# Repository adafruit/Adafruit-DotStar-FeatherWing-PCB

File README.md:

## Adafruit DotStar FeatherWing PCB

<a href="http://www.adafruit.com/products/3449"><br/>
Click here to purchase one from the Adafruit shop</a>

PCB files for the Adafruit DotStar FeatherWing. Format is EagleCAD schematic and board layout

For more details, check out the product page at
* http://www.adafruit.com/products/3449

### Description

A Feather board without ambition is a Feather board without FeatherWings! This is the DotStar FeatherWing, a 6x12 RGB LED Add-on For All Feather Boards! Using our Feather Stacking Headers or Feather Female Headers you can connect a FeatherWing on top or bottom of your Feather board and make your Feather board strut like a peacock at a rave.

Put on your sunglasses before staring into these 72 configurable RGB LEDs, they are super bright! Arranged in a 6x12 matrix, each 2mm by 2mm sized RGB pixel is individually addressable. Only two pins are required to control all the LEDs. On the bottom we have jumpers for the Data and Clock lines so you can change them from the defaults. Works with any/all of our Feathers! You can cut the default jumper traces and use any pins you like

To make it easy to start, the LEDs are by default powered from either the USB power line or Battery power line, whichever is higher. Two Schottky diodes are used to switch between the two. This power arrangement is able to handle 1 Amp of constant current draw and maybe 2A peak, so not a good way to make a flashlight. It's better for colorful effects. A power MOSFET is set up and connected to the ENABLE pin on the Feather so that when the Feather is disabled, the wing will also cut power.

### License

Adafruit invests time and resources providing this open source design, please support Adafruit and open-source hardware by purchasing products from [Adafruit](https://www.adafruit.com)!

Designed by Limor Fried/Ladyada for Adafruit Industries.

Creative Commons Attribution/Share-Alike, all text above must be included in any redistribution. See license.txt for additional details.

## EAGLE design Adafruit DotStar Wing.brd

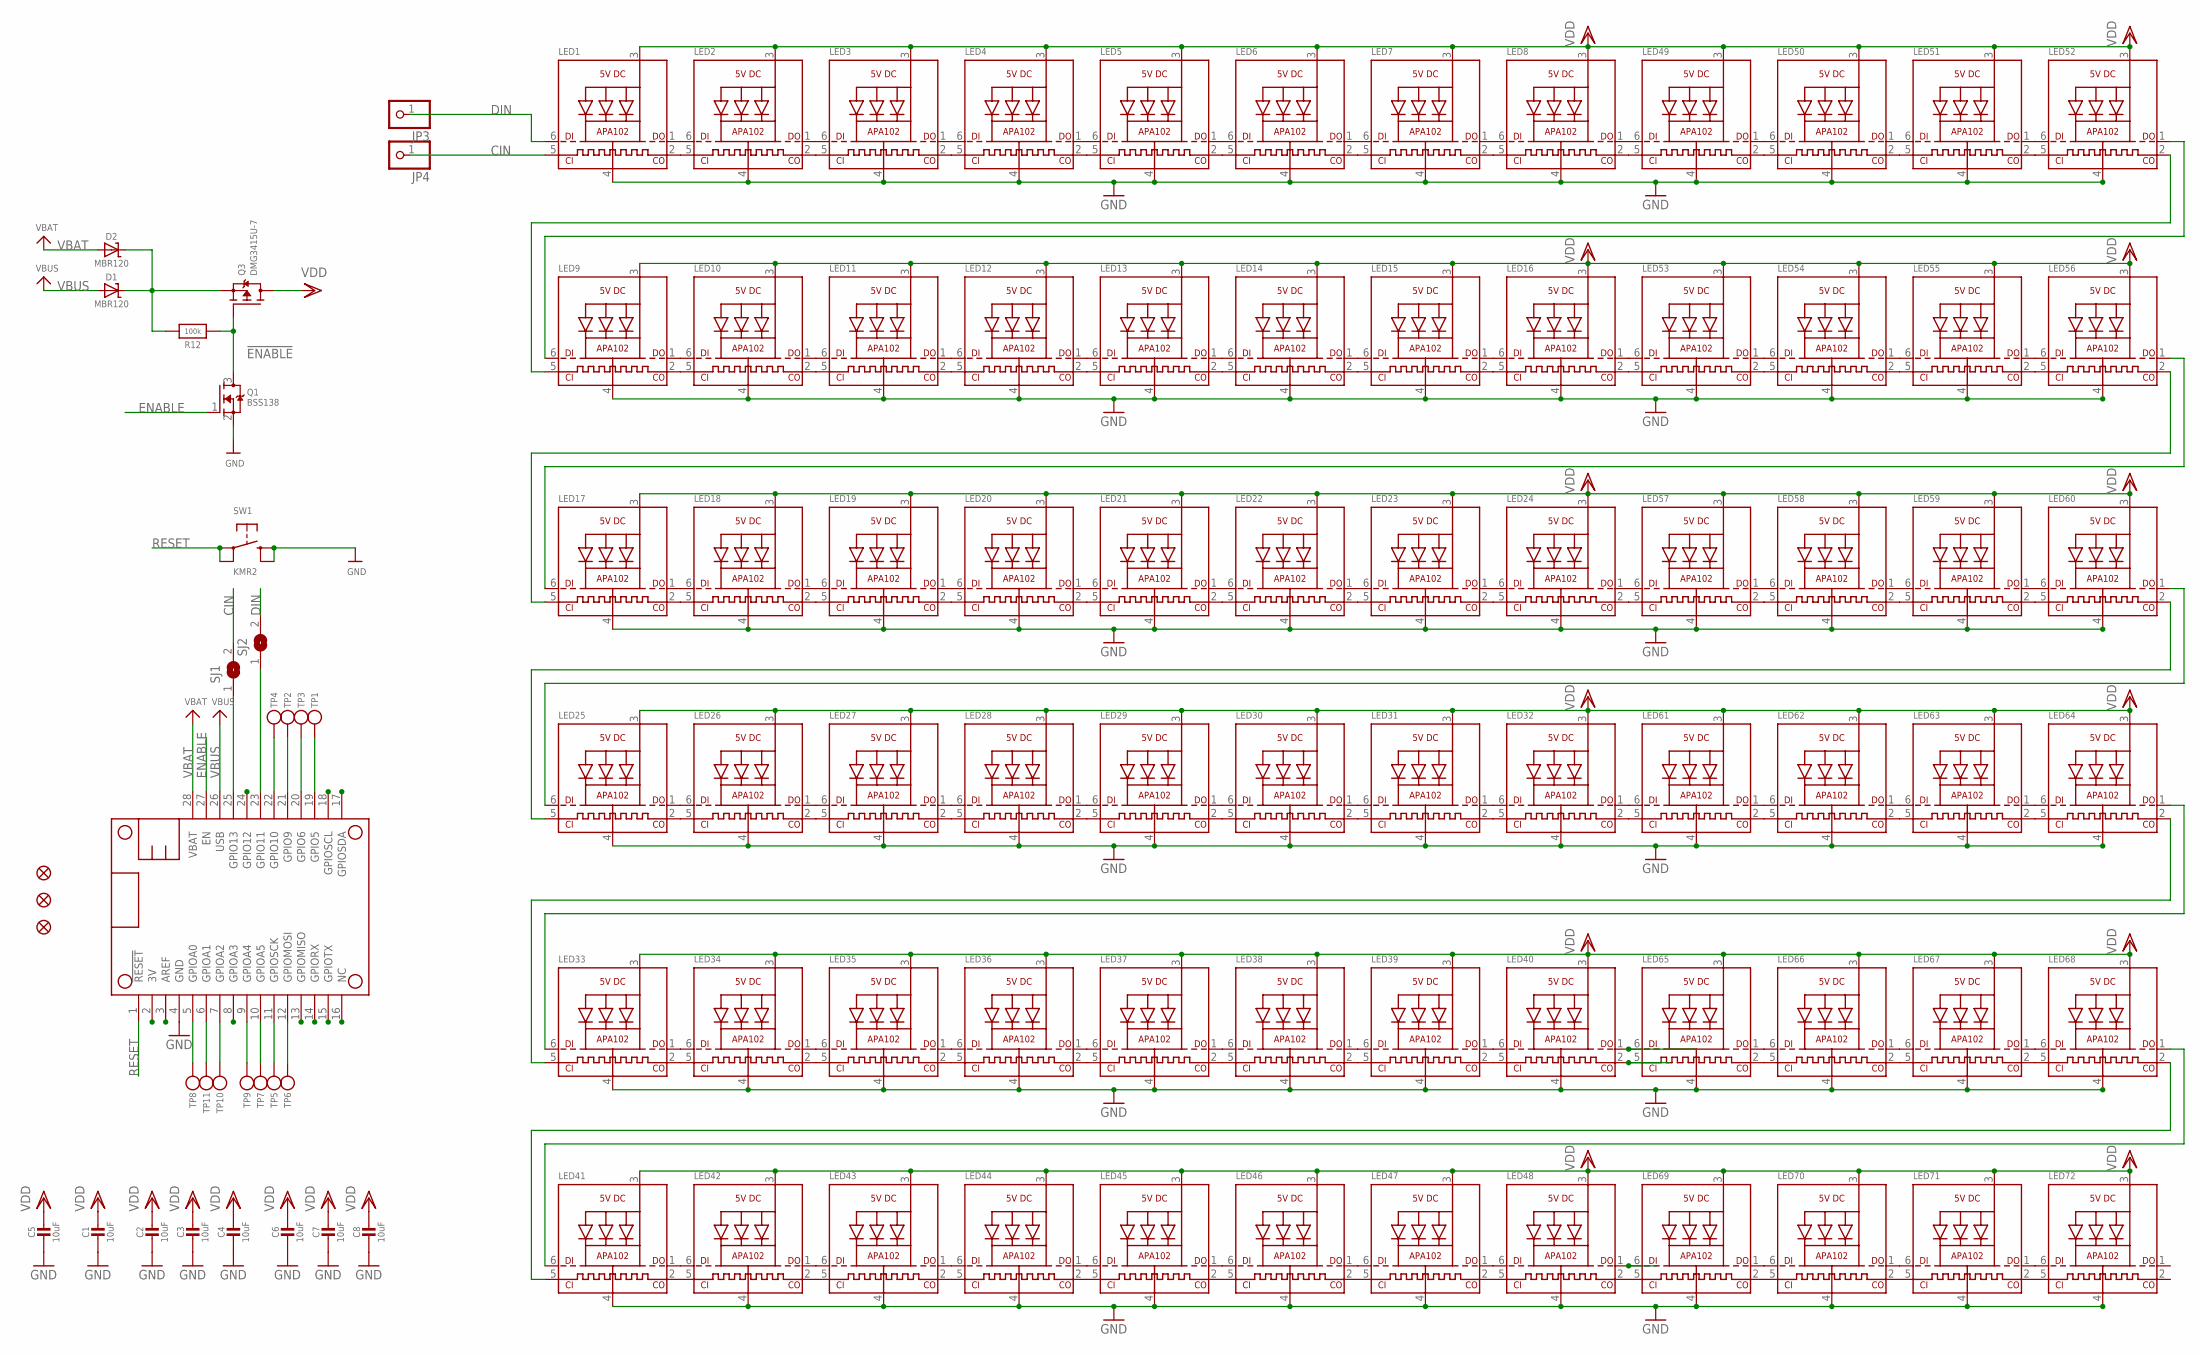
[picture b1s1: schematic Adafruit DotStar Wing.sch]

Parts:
C1, C2, C3, C4, C5, C6, C7, C8: 10uF; 0805-NO
D1, D2: MBR120; SOD-123
FID1, FID2, FID3: FIDUCIAL_1MM
JP3, JP4: HEADER-1X1ROUND; 1X01_ROUND
LED1, LED2, LED3, LED4, LED5, LED6, LED7, LED8, LED9, LED10, LED11, LED12, LED13, LED14, LED15, LED16, LED17, LED18, LED19, LED20, LED21, LED22, LED23, LED24, LED25, LED26, LED27, LED28, LED29, LED30, LED31, LED32, LED33, LED34, LED35, LED36, LED37, LED38, LED39, LED40, LED41, LED42, LED43, LED44, LED45, LED46, LED47, LED48, LED49, LED50, LED51, LED52, LED53, LED54, LED55, LED56, LED57, LED58, LED59, LED60, LED61, LED62, LED63, LED64, LED65, LED66, LED67, LED68, LED69, LED70, LED71, LED72: APA1022020; APA102_2020
MS1: FEATHERWING
Q1: BSS138; SOT23-WIDE
Q3: DMG3415U-7; SOT23-WIDE
R12: 100k; 0603-NO
SJ1, SJ2: SOLDERJUMPERCLOSED; SOLDERJUMPER_CLOSEDWIRE
SW1: KMR2; BTN_KMR2_4.6X2.8
TP1, TP2, TP3, TP4, TP5, TP6, TP7, TP8, TP9, TP10, TP11: TESTPOINT1.5X2.0MM_NOCREAM; PAD-1.5X2.0

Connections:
3V: MS1.2 (3V)
!ENABLE: Q1.3 (D), Q3.1 (G), R12.1
A0: MS1.5 (GPIOA0), TP8.P$1
A1: MS1.6 (GPIOA1), TP11.P$1
A2: MS1.7 (GPIOA2), TP10.P$1
A3: MS1.8 (GPIOA3)
A4: MS1.9 (GPIOA4), TP9.P$1
A5: MS1.10 (GPIOA5), TP7.P$1
AREF: MS1.3 (AREF)
CIN: JP4.1, LED1.5 (CKI), SJ1.2
DIN: JP3.1, LED1.6 (DI), SJ2.2
ENABLE: MS1.27 (EN), Q1.1 (G)
G: MS1.16 (NC)
GND: C1.2, C2.2, C3.2, C4.2, C5.2, C6.2, C7.2, C8.2, LED1.4 (GND), LED2.4 (GND), LED3.4 (GND), LED4.4 (GND), LED5.4 (GND), LED6.4 (GND), LED7.4 (GND), LED8.4 (GND), LED9.4 (GND), LED10.4 (GND), LED11.4 (GND), LED12.4 (GND), LED13.4 (GND), LED14.4 (GND), LED15.4 (GND), LED16.4 (GND), LED17.4 (GND), LED18.4 (GND), LED19.4 (GND), LED20.4 (GND), LED21.4 (GND), LED22.4 (GND), LED23.4 (GND), LED24.4 (GND), LED25.4 (GND), LED26.4 (GND), LED27.4 (GND), LED28.4 (GND), LED29.4 (GND), LED30.4 (GND), LED31.4 (GND), LED32.4 (GND), LED33.4 (GND), LED34.4 (GND), LED35.4 (GND), LED36.4 (GND), LED37.4 (GND), LED38.4 (GND), LED39.4 (GND), LED40.4 (GND), LED41.4 (GND), LED42.4 (GND), LED43.4 (GND), LED44.4 (GND), LED45.4 (GND), LED46.4 (GND), LED47.4 (GND), LED48.4 (GND), LED49.4 (GND), LED50.4 (GND), LED51.4 (GND), LED52.4 (GND), LED53.4 (GND), LED54.4 (GND), LED55.4 (GND), LED56.4 (GND), LED57.4 (GND), LED58.4 (GND), LED59.4 (GND), LED60.4 (GND), LED61.4 (GND), LED62.4 (GND), LED63.4 (GND), LED64.4 (GND), LED65.4 (GND), LED66.4 (GND), LED67.4 (GND), LED68.4 (GND), LED69.4 (GND), LED70.4 (GND), LED71.4 (GND), LED72.4 (GND), MS1.4 (GND), Q1.2 (S), SW1.B (S), SW1.B' (S1)
H: MS1.19 (GPIO5), TP1.P$1
I: MS1.20 (GPIO6), TP3.P$1
J: MS1.21 (GPIO9), TP2.P$1
K: MS1.22 (GPIO10), TP4.P$1
L: MS1.23 (GPIO11), SJ2.1
M: MS1.24 (GPIO12)
MISO: MS1.13 (GPIOMISO)
MOSI: MS1.12 (GPIOMOSI), TP6.P$1
N: MS1.25 (GPIO13), SJ1.1
unnamed: LED1.1 (DO), LED2.6 (DI)
unnamed: LED1.2 (CKO), LED2.5 (CKI)
unnamed: LED2.1 (DO), LED3.6 (DI)
unnamed: LED2.2 (CKO), LED3.5 (CKI)
unnamed: LED3.1 (DO), LED4.6 (DI)
unnamed: LED3.2 (CKO), LED4.5 (CKI)
unnamed: LED4.1 (DO), LED5.6 (DI)
unnamed: LED4.2 (CKO), LED5.5 (CKI)
unnamed: LED5.1 (DO), LED6.6 (DI)
unnamed: LED5.2 (CKO), LED6.5 (CKI)
unnamed: LED6.1 (DO), LED7.6 (DI)
unnamed: LED6.2 (CKO), LED7.5 (CKI)
unnamed: LED7.1 (DO), LED8.6 (DI)
unnamed: LED7.2 (CKO), LED8.5 (CKI)
unnamed: LED9.1 (DO), LED10.6 (DI)
unnamed: LED9.2 (CKO), LED10.5 (CKI)
unnamed: LED10.1 (DO), LED11.6 (DI)
unnamed: LED10.2 (CKO), LED11.5 (CKI)
unnamed: LED11.1 (DO), LED12.6 (DI)
unnamed: LED11.2 (CKO), LED12.5 (CKI)
unnamed: LED12.1 (DO), LED13.6 (DI)
unnamed: LED12.2 (CKO), LED13.5 (CKI)
unnamed: LED13.1 (DO), LED14.6 (DI)
unnamed: LED13.2 (CKO), LED14.5 (CKI)
unnamed: LED14.1 (DO), LED15.6 (DI)
unnamed: LED14.2 (CKO), LED15.5 (CKI)
unnamed: LED15.1 (DO), LED16.6 (DI)
unnamed: LED15.2 (CKO), LED16.5 (CKI)
unnamed: LED17.1 (DO), LED18.6 (DI)
unnamed: LED17.2 (CKO), LED18.5 (CKI)
unnamed: LED18.1 (DO), LED19.6 (DI)
unnamed: LED18.2 (CKO), LED19.5 (CKI)
unnamed: LED19.1 (DO), LED20.6 (DI)
unnamed: LED19.2 (CKO), LED20.5 (CKI)
unnamed: LED20.1 (DO), LED21.6 (DI)
unnamed: LED20.2 (CKO), LED21.5 (CKI)
unnamed: LED21.1 (DO), LED22.6 (DI)
unnamed: LED21.2 (CKO), LED22.5 (CKI)
unnamed: LED22.1 (DO), LED23.6 (DI)
unnamed: LED22.2 (CKO), LED23.5 (CKI)
unnamed: LED23.1 (DO), LED24.6 (DI)
unnamed: LED23.2 (CKO), LED24.5 (CKI)
unnamed: LED25.1 (DO), LED26.6 (DI)
unnamed: LED25.2 (CKO), LED26.5 (CKI)
unnamed: LED26.1 (DO), LED27.6 (DI)
unnamed: LED26.2 (CKO), LED27.5 (CKI)
unnamed: LED27.1 (DO), LED28.6 (DI)
unnamed: LED27.2 (CKO), LED28.5 (CKI)
unnamed: LED28.1 (DO), LED29.6 (DI)
unnamed: LED28.2 (CKO), LED29.5 (CKI)
unnamed: LED29.1 (DO), LED30.6 (DI)
unnamed: LED29.2 (CKO), LED30.5 (CKI)
unnamed: LED30.1 (DO), LED31.6 (DI)
unnamed: LED30.2 (CKO), LED31.5 (CKI)
unnamed: LED31.1 (DO), LED32.6 (DI)
unnamed: LED31.2 (CKO), LED32.5 (CKI)
unnamed: LED33.1 (DO), LED34.6 (DI)
unnamed: LED33.2 (CKO), LED34.5 (CKI)
unnamed: LED34.1 (DO), LED35.6 (DI)
unnamed: LED34.2 (CKO), LED35.5 (CKI)
unnamed: LED35.1 (DO), LED36.6 (DI)
unnamed: LED35.2 (CKO), LED36.5 (CKI)
unnamed: LED36.1 (DO), LED37.6 (DI)
unnamed: LED36.2 (CKO), LED37.5 (CKI)
unnamed: LED37.1 (DO), LED38.6 (DI)
unnamed: LED37.2 (CKO), LED38.5 (CKI)
unnamed: LED38.1 (DO), LED39.6 (DI)
unnamed: LED38.2 (CKO), LED39.5 (CKI)
unnamed: LED39.1 (DO), LED40.6 (DI)
unnamed: LED39.2 (CKO), LED40.5 (CKI)
unnamed: LED41.1 (DO), LED42.6 (DI)
unnamed: LED41.2 (CKO), LED42.5 (CKI)
unnamed: LED42.1 (DO), LED43.6 (DI)
unnamed: LED42.2 (CKO), LED43.5 (CKI)
unnamed: LED43.1 (DO), LED44.6 (DI)
unnamed: LED43.2 (CKO), LED44.5 (CKI)
unnamed: LED44.1 (DO), LED45.6 (DI)
unnamed: LED44.2 (CKO), LED45.5 (CKI)
unnamed: LED45.1 (DO), LED46.6 (DI)
unnamed: LED45.2 (CKO), LED46.5 (CKI)
unnamed: LED46.1 (DO), LED47.6 (DI)
unnamed: LED46.2 (CKO), LED47.5 (CKI)
unnamed: LED47.1 (DO), LED48.6 (DI)
unnamed: LED47.2 (CKO), LED48.5 (CKI)
unnamed: LED8.1 (DO), LED49.6 (DI)
unnamed: LED8.2 (CKO), LED49.5 (CKI)
unnamed: LED49.1 (DO), LED50.6 (DI)
unnamed: LED49.2 (CKO), LED50.5 (CKI)
unnamed: LED50.1 (DO), LED51.6 (DI)
unnamed: LED50.2 (CKO), LED51.5 (CKI)
unnamed: LED51.1 (DO), LED52.6 (DI)
unnamed: LED51.2 (CKO), LED52.5 (CKI)
unnamed: LED16.1 (DO), LED53.6 (DI)
unnamed: LED16.2 (CKO), LED53.5 (CKI)
unnamed: LED53.1 (DO), LED54.6 (DI)
unnamed: LED53.2 (CKO), LED54.5 (CKI)
unnamed: LED54.1 (DO), LED55.6 (DI)
unnamed: LED54.2 (CKO), LED55.5 (CKI)
unnamed: LED55.1 (DO), LED56.6 (DI)
unnamed: LED55.2 (CKO), LED56.5 (CKI)
unnamed: LED24.1 (DO), LED57.6 (DI)
unnamed: LED24.2 (CKO), LED57.5 (CKI)
unnamed: LED57.1 (DO), LED58.6 (DI)
unnamed: LED57.2 (CKO), LED58.5 (CKI)
unnamed: LED58.1 (DO), LED59.6 (DI)
unnamed: LED58.2 (CKO), LED59.5 (CKI)
unnamed: LED59.1 (DO), LED60.6 (DI)
unnamed: LED59.2 (CKO), LED60.5 (CKI)
unnamed: LED61.1 (DO), LED62.6 (DI)
unnamed: LED61.2 (CKO), LED62.5 (CKI)
unnamed: LED62.1 (DO), LED63.6 (DI)
unnamed: LED62.2 (CKO), LED63.5 (CKI)
unnamed: LED9.5 (CKI), LED52.2 (CKO)
unnamed: LED17.6 (DI), LED56.1 (DO)
unnamed: LED17.5 (CKI), LED56.2 (CKO)
unnamed: LED25.5 (CKI), LED60.2 (CKO)
unnamed: LED33.6 (DI), LED64.1 (DO)
unnamed: LED63.1 (DO), LED64.6 (DI)
unnamed: LED63.2 (CKO), LED64.5 (CKI)
unnamed: LED65.1 (DO), LED66.6 (DI)
unnamed: LED48.1 (DO), LED69.6 (DI)
unnamed: LED41.5 (CKI), LED68.2 (CKO)
unnamed: LED41.6 (DI), LED68.1 (DO)
unnamed: LED65.2 (CKO), LED66.5 (CKI)
unnamed: LED66.1 (DO), LED67.6 (DI)
unnamed: LED66.2 (CKO), LED67.5 (CKI)
unnamed: LED67.1 (DO), LED68.6 (DI)
unnamed: LED67.2 (CKO), LED68.5 (CKI)
unnamed: LED69.1 (DO), LED70.6 (DI)
unnamed: LED69.2 (CKO), LED70.5 (CKI)
unnamed: LED70.1 (DO), LED71.6 (DI)
unnamed: LED70.2 (CKO), LED71.5 (CKI)
unnamed: LED71.1 (DO), LED72.6 (DI)
unnamed: LED71.2 (CKO), LED72.5 (CKI)
unnamed: LED9.6 (DI), LED52.1 (DO)
unnamed: D1.C, D2.C, Q3.2 (S), R12.2
unnamed: LED32.2 (CKO), LED61.5 (CKI)
unnamed: LED32.1 (DO), LED61.6 (DI)
unnamed: LED25.6 (DI), LED60.1 (DO)
unnamed: LED33.5 (CKI), LED64.2 (CKO)
unnamed: LED48.2 (CKO), LED69.5 (CKI)
unnamed: LED40.2 (CKO), LED65.5 (CKI)
unnamed: LED40.1 (DO), LED65.6 (DI)
RESET: MS1.1 (!RESET), SW1.A, SW1.A' (P1)
RX: MS1.14 (GPIORX)
SCK: MS1.11 (GPIOSCK), TP5.P$1
SCL: MS1.18 (GPIOSCL)
SDA: MS1.17 (GPIOSDA)
TX: MS1.15 (GPIOTX)
VBAT: D2.A, MS1.28 (VBAT)
VBUS: D1.A, MS1.26 (USB)
VDD: C1.1, C2.1, C3.1, C4.1, C5.1, C6.1, C7.1, C8.1, LED1.3 (VDD), LED2.3 (VDD), LED3.3 (VDD), LED4.3 (VDD), LED5.3 (VDD), LED6.3 (VDD), LED7.3 (VDD), LED8.3 (VDD), LED9.3 (VDD), LED10.3 (VDD), LED11.3 (VDD), LED12.3 (VDD), LED13.3 (VDD), LED14.3 (VDD), LED15.3 (VDD), LED16.3 (VDD), LED17.3 (VDD), LED18.3 (VDD), LED19.3 (VDD), LED20.3 (VDD), LED21.3 (VDD), LED22.3 (VDD), LED23.3 (VDD), LED24.3 (VDD), LED25.3 (VDD), LED26.3 (VDD), LED27.3 (VDD), LED28.3 (VDD), LED29.3 (VDD), LED30.3 (VDD), LED31.3 (VDD), LED32.3 (VDD), LED33.3 (VDD), LED34.3 (VDD), LED35.3 (VDD), LED36.3 (VDD), LED37.3 (VDD), LED38.3 (VDD), LED39.3 (VDD), LED40.3 (VDD), LED41.3 (VDD), LED42.3 (VDD), LED43.3 (VDD), LED44.3 (VDD), LED45.3 (VDD), LED46.3 (VDD), LED47.3 (VDD), LED48.3 (VDD), LED49.3 (VDD), LED50.3 (VDD), LED51.3 (VDD), LED52.3 (VDD), LED53.3 (VDD), LED54.3 (VDD), LED55.3 (VDD), LED56.3 (VDD), LED57.3 (VDD), LED58.3 (VDD), LED59.3 (VDD), LED60.3 (VDD), LED61.3 (VDD), LED62.3 (VDD), LED63.3 (VDD), LED64.3 (VDD), LED65.3 (VDD), LED66.3 (VDD), LED67.3 (VDD), LED68.3 (VDD), LED69.3 (VDD), LED70.3 (VDD), LED71.3 (VDD), LED72.3 (VDD), Q3.3 (D)

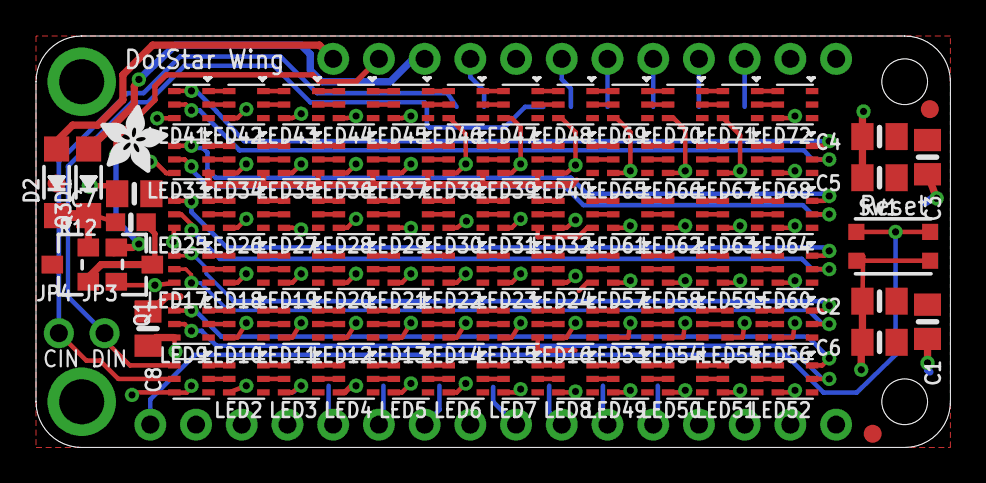
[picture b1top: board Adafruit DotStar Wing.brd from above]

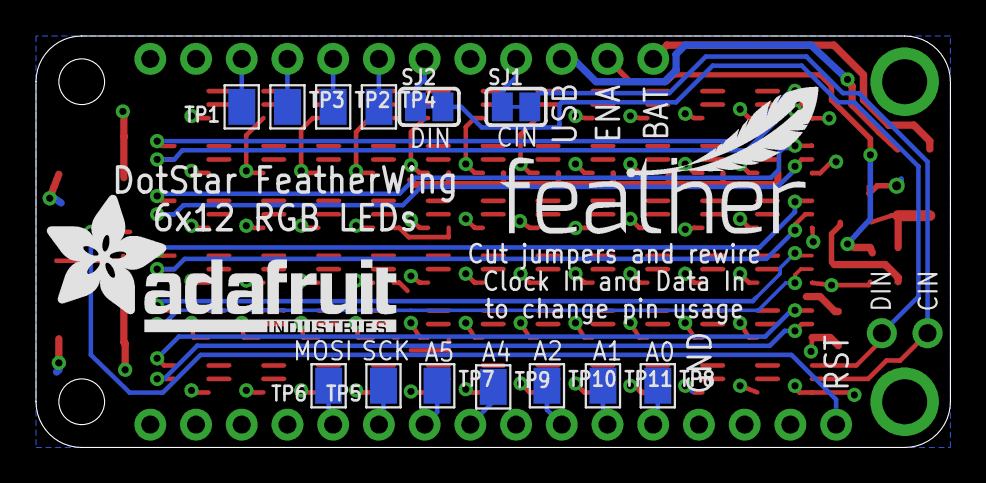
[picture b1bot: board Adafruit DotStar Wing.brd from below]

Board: 2 copper layers, 50.8 x 22.9 mm, 108 parts (15 on the bottom side), 165 nets.

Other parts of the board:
U$1: ADAFRUIT_TEXT_20MM
U$8: FEATHERLOGO_MED
U$9: ADAFRUIT_3.5MM

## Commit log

2017-10-02 init
2017-10-02 read

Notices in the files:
parts and their libraries:
microbuilder: This work is placed in the public domain, and may be freely used for commercial and non-commercial work with the following conditions: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
